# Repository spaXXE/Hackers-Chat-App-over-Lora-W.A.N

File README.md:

# Under rigorous Development...

***
### Watch out for exclusive tech. coming your way😎!

***

```py
    import time 

    def development():
        
        while 1:
            time.delay()
            break # DISCLAIMER: Heads up, will break soon...

    development()
```
***

***

   ### As an appetiser, we humbly offer you.....

***

## The Project's Structure.

## The Sofware's Components and Structure Model.

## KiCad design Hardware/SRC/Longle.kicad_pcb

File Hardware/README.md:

# LoRa Dongle

The hardware is a USB 2.0 fullspeed device with an STM32F042K6 MCU and 433MHz LoRa module based on the SX1278. Onboard EEPROM memory provides persistent storage of received messages and buffering of sent messages that have not been acknowledged to have been received by the sender.

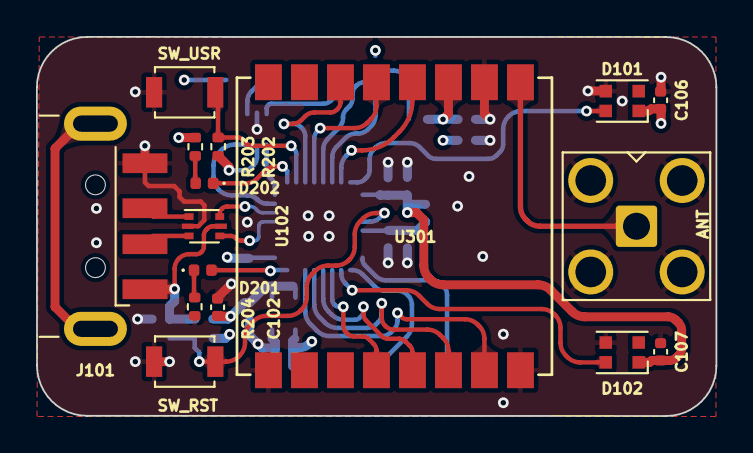
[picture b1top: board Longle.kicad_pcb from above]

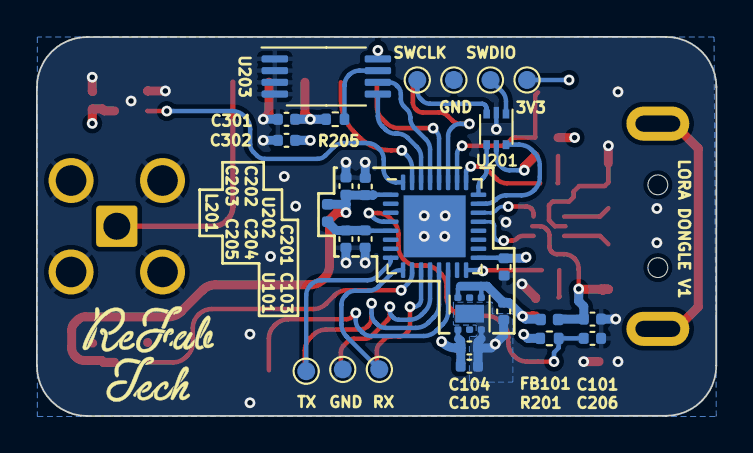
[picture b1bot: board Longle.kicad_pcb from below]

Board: 4 copper layers, 37.7 x 21.1 mm, 43 parts (27 on the bottom side), 34 nets.

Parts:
AE301: Antenna_Shield; SMA_Amphenol_901-143_Horizontal
C101, C102, C103, C104, C203, C204, C206, C301: 2u2; C_0402_1005Metric
C105, C106, C107, C201, C202, C205, C302: 100n; C_0402_1005Metric
D101, D102: WS2812B; LED_WS2812B-2020_PLCC4_2.0x2.0mm
D201: LED_O; LED_0402_1005Metric
D202: LED_B; LED_0402_1005Metric
FB101: 220R@100MHz 1A; L_0402_1005Metric
J101: USB_A; USB_A_CNCTech_1001-011-01101_Horizontal
L201: 10u; L_0402_1005Metric
R201, R202, R205: 10K 0.1%; R_0402_1005Metric
R203, R204: 1K 0.1%; R_0402_1005Metric
SW201: SW_RST; SW_SPST_B3U-1000P
SW202: SW_USER; SW_SPST_B3U-1000P
TP201: TP_3V3; TestPoint_Pad_D1.0mm
TP202: TP_SWDIO; TestPoint_Pad_D1.0mm
TP203: TP_GND1; TestPoint_Pad_D1.0mm
TP204: TP_SWCLK; TestPoint_Pad_D1.0mm
TP205: TP_TX; TestPoint_Pad_D1.0mm
TP206: TP_RX; TestPoint_Pad_D1.0mm
TP207: TP_GND2; TestPoint_Pad_D1.0mm
U101: TLV75533PDRV; WSON-6-1EP_2x2mm_P0.65mm_EP1x1.6mm
U102, U201: USBLC6-2P6; SOT-666
U202: STM32F042K6Ux; QFN-32-1EP_5x5mm_P0.5mm_EP3.45x3.45mm
U203: 24LC1025; TSSOP-8_4.4x3mm_P0.65mm
U301: Ai-Thinker-Ra-01; Ai-Thinker-Ra-01-LoRa

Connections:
+3V3: C104.1, C105.1, C106.1, C107.1, C201.1, C202.1, C203.1, C301.1, C302.1, D101.1 (VDD), D102.1 (VDD), L201.1, R201.1, R202.2, R203.2, R205.1, TP201.1, U101.1 (OUT), U201.5 (VBUS), U202.1 (VDD), U202.17 (VDDIO2), U203.8 (VCC), U301.3 (VDD)
+5V: C102.1, C103.1, FB101.2, U101.4 (EN), U101.6 (IN)
/D+: J101.3 (D+), U102.1 (I/O1)
/D-: J101.2 (D-), U102.3 (I/O2)
/RF_LORA_RA-01/ANT: AE301.1 (A), U301.1 (ANT)
/RF_LORA_RA-01/LORA_DIO0: U202.28 (PB5), U301.5 (DIO0)
/RF_LORA_RA-01/LORA_DIO1: U202.27 (PB4), U301.6 (DIO1)
/RF_LORA_RA-01/LORA_MISO: U202.12 (PA6), U301.13 (MISO)
/RF_LORA_RA-01/LORA_MOSI: U202.13 (PA7), U301.14 (MOSI)
/RF_LORA_RA-01/LORA_NCS: U202.14 (PB0), U301.15 (~NSS)
/RF_LORA_RA-01/LORA_RST: U202.31 (PF11), U301.4 (~RESET)
/RF_LORA_RA-01/LORA_SCK: U202.11 (PA5), U301.12 (SCK)
/STM32F042K6/BTN: R202.1, SW202.1, U202.26 (PB3)
/STM32F042K6/I2C1_SCL: U202.29 (PB6), U203.6 (SCL)
/STM32F042K6/I2C1_SDA: U202.30 (PB7), U203.5 (SDA)
/STM32F042K6/LED: D201.2 (A), U202.16 (PB2)
/STM32F042K6/NRST: C206.1, R201.2, SW201.2, U202.4 (NRST)
/STM32F042K6/SWCLK: U201.4 (I/O2), U202.24 (PA14)
/STM32F042K6/SWCLK_IN: TP204.1, U201.3 (I/O2)
/STM32F042K6/SWDIO: U201.6 (I/O1), U202.23 (PA13)
/STM32F042K6/SWDIO_IN: TP202.1, U201.1 (I/O1)
/STM32F042K6/USART2_RX: TP206.1, U202.9 (PA3)
/STM32F042K6/USART2_TX: TP205.1, U202.8 (PA2)
/STM32F042K6/USB_NOE: D202.1 (K), U202.25 (PA15)
/STM32F042K6/WS2812_1: D102.4 (DIN), U202.10 (PA4)
/STM32F042K6/WS2812_2: D101.4 (DIN), U202.32 (PB8)
/USB_DN: U102.4 (I/O2), U202.21 (PA11)
/USB_DP: U102.6 (I/O1), U202.22 (PA12)
GND: AE301.2 (Shield), C101.2, C102.2, C103.2, C104.2, C105.2, C106.2, C107.2, C201.2, C202.2, C203.2, C204.2, C205.2, C206.2, C301.2, C302.2, D101.3 (VSS), D102.3 (VSS), J101.4 (GND), R204.1, SW201.1, SW202.2, TP203.1, TP207.1, U101.3 (GND), U101.7 (GND), U102.2 (GND), U201.2 (GND), U202.33 (VSS), U203.1 (A0), U203.2 (A1), U203.3 (A2), U203.4 (GND), U301.2 (GND), U301.9 (GND), U301.16 (GND)
unnamed: D201.1 (K), R204.2
unnamed: D202.2 (A), R203.1
unnamed: R205.2, U203.7 (WP)
VBUS: C101.1, FB101.1, J101.1 (VBUS), U102.5 (VBUS)
VDDA: C204.1, C205.1, L201.2, U202.5 (VDDA)

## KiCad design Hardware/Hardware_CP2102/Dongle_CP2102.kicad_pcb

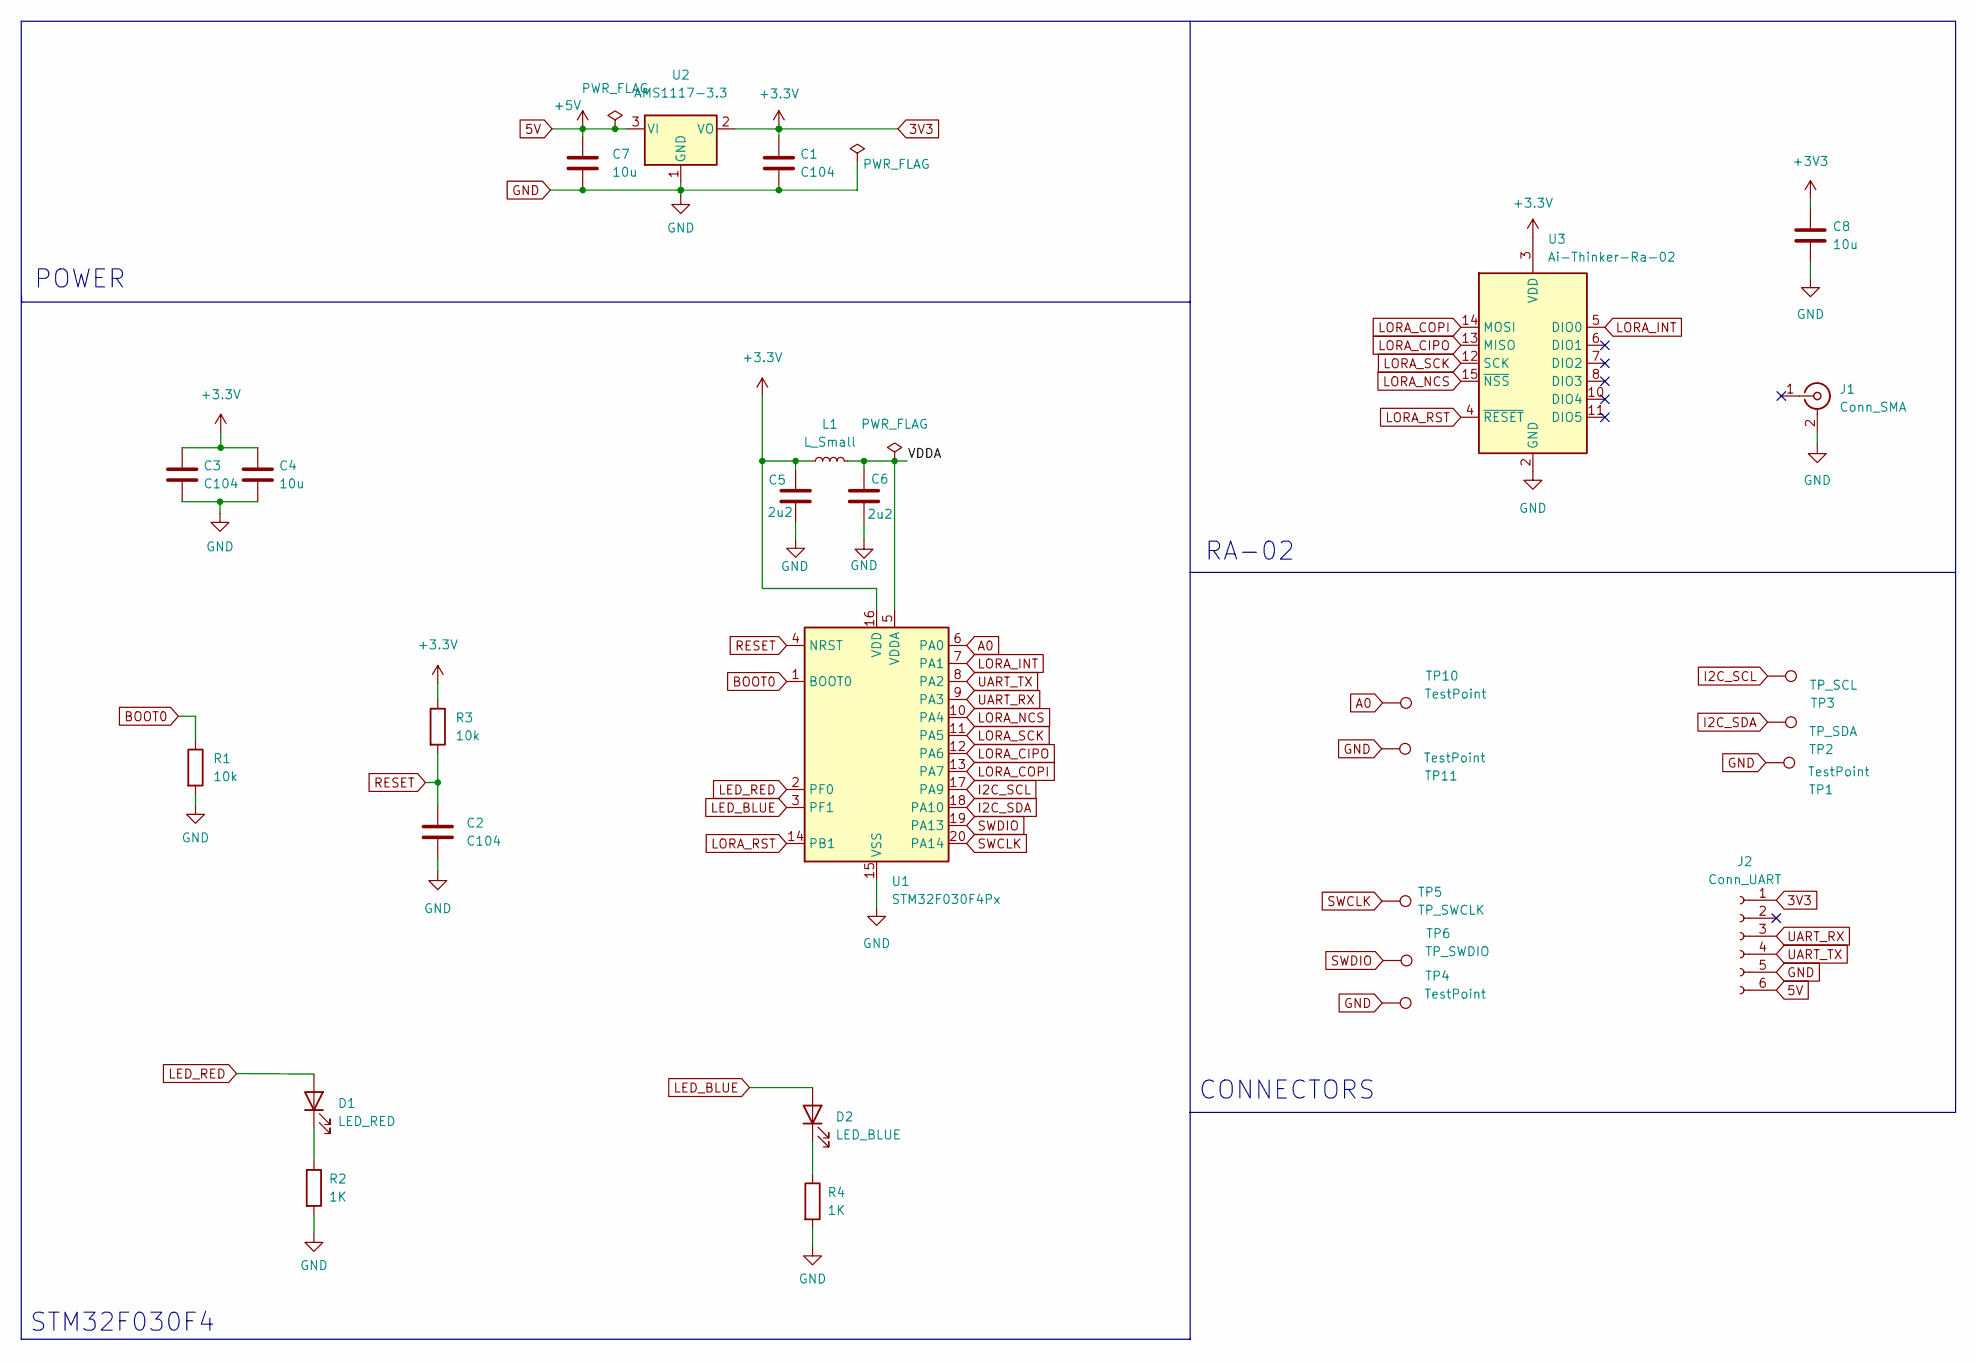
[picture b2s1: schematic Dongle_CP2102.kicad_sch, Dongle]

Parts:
C1, C2, C3: C104; C_0805_2012Metric_Pad1.18x1.45mm_HandSolder
C4, C7, C8: 10u; C_0805_2012Metric_Pad1.18x1.45mm_HandSolder
C5, C6: 2u2; C_0805_2012Metric_Pad1.18x1.45mm_HandSolder
D1: LED_RED; LED_0805_2012Metric_Pad1.15x1.40mm_HandSolder
D2: LED_BLUE; LED_0805_2012Metric_Pad1.15x1.40mm_HandSolder
J1: Conn_SMA; SMA_Amphenol_901-144_Vertical
J2: Conn_UART; PinSocket_1x06_P2.54mm_Horizontal
L1: L_Small; L_0805_2012Metric_Pad1.15x1.40mm_HandSolder
R1, R3: 10k; R_0805_2012Metric_Pad1.20x1.40mm_HandSolder
R2, R4: 1K; R_0805_2012Metric_Pad1.20x1.40mm_HandSolder
TP1, TP4, TP10, TP11: TestPoint; TestPoint_Pad_D1.5mm
TP2: TP_SDA; TestPoint_Pad_D1.5mm
TP3: TP_SCL; TestPoint_Pad_D1.5mm
TP5: TP_SWCLK; TestPoint_Pad_D1.5mm
TP6: TP_SWDIO; TestPoint_Pad_D1.5mm
U1: STM32F030F4Px; TSSOP-20_4.4x6.5mm_P0.65mm
U2: AMS1117-3.3; SOT-223-3_TabPin2
U3: Ai-Thinker-Ra-02; Ai-Thinker-Ra-01-LoRa

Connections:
3V3: C1.1, C3.1, C4.1, C5.1, C8.1, J2.1, L1.1, R3.1, U1.16 (VDD), U2.2 (VO), U3.3 (VDD)
5V: C7.1, J2.6, U2.3 (VI)
/VDDA: C6.1, L1.2, U1.5 (VDDA)
A0: TP10.1, U1.6 (PA0)
BOOT0: R1.1, U1.1 (BOOT0)
GND: C1.2, C2.2, C3.2, C4.2, C5.2, C6.2, C7.2, C8.2, J1.2 (Ext), J2.5, R1.2, R2.2, R4.2, TP1.1, TP4.1, TP11.1, U1.15 (VSS), U2.1 (GND), U3.1 (GND), U3.2 (GND), U3.9 (GND), U3.16 (GND)
I2C_SCL: TP3.1, U1.17 (PA9)
I2C_SDA: TP2.1, U1.18 (PA10)
LED_BLUE: D2.2 (A), U1.3 (PF1)
LED_RED: D1.2 (A), U1.2 (PF0)
LORA_CIPO: U1.12 (PA6), U3.13 (MISO)
LORA_COPI: U1.13 (PA7), U3.14 (MOSI)
LORA_INT: U1.7 (PA1), U3.5 (DIO0)
LORA_NCS: U1.10 (PA4), U3.15 (~NSS)
LORA_RST: U1.14 (PB1), U3.4 (~RESET)
LORA_SCK: U1.11 (PA5), U3.12 (SCK)
unnamed: D1.1 (K), R2.1
unnamed: D2.1 (K), R4.1
RESET: C2.1, R3.2, U1.4 (NRST)
SWCLK: TP5.1, U1.20 (PA14)
SWDIO: TP6.1, U1.19 (PA13)
UART_RX: J2.3, U1.9 (PA3)
UART_TX: J2.4, U1.8 (PA2)

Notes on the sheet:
STM32F030F4
CONNECTORS
RA-02
POWER

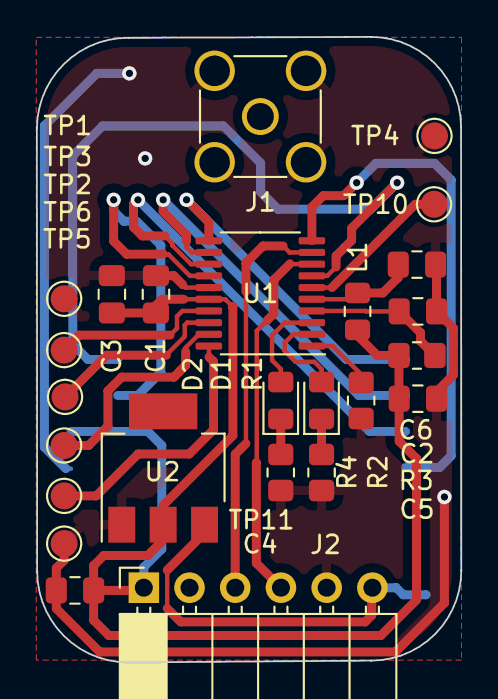
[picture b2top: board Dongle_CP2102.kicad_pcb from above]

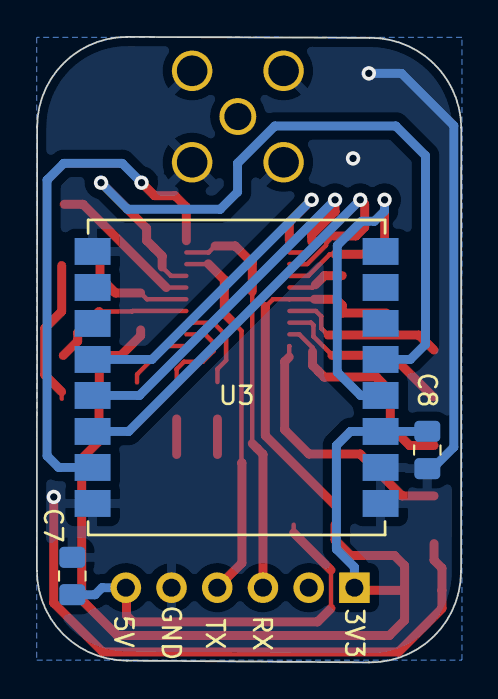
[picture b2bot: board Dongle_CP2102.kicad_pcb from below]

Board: 2 copper layers, 23.6 x 34.8 mm, 28 parts (3 on the bottom side), 23 nets.

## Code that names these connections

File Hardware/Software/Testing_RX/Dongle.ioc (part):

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Mcu.Name=STM32F030F4Px
Mcu.Package=TSSOP20
Mcu.UserName=STM32F030F4Px
PA0.Mode=IN0
PA0.Signal=ADC_IN0
PA1.GPIOParameters=GPIO_Label
PA1.GPIO_Label=LORA_INT
PA1.Signal=GPXTI1
PA10.Mode=I2C
PA10.Signal=I2C1_SDA
PA13.Mode=Serial_Wire
PA13.Signal=SYS_SWDIO
PA14.Mode=Serial_Wire
PA14.Signal=SYS_SWCLK
PA2.Mode=Asynchronous
PA2.Signal=USART1_TX
PA3.Mode=Asynchronous
PA3.Signal=USART1_RX
PA4.GPIOParameters=GPIO_Label
PA4.GPIO_Label=LORA_NCS
PA4.Signal=GPIO_Output
PA5.GPIOParameters=GPIO_Label
PA5.GPIO_Label=LORA_SCK
PA5.Mode=Full_Duplex_Master
PA5.Signal=SPI1_SCK
PA6.GPIOParameters=GPIO_Label
PA6.GPIO_Label=LORA_CIPO
PA6.Mode=Full_Duplex_Master
PA6.Signal=SPI1_MISO
PA7.GPIOParameters=GPIO_Label
PA7.GPIO_Label=LORA_COPI
PA7.Mode=Full_Duplex_Master
PA7.Signal=SPI1_MOSI
PA9.Mode=I2C
PA9.Signal=I2C1_SCL
PB1.GPIOParameters=GPIO_Label
PB1.GPIO_Label=LORA_RST
PB1.Signal=GPIO_Output
PF0-OSC_IN.GPIOParameters=GPIO_Label
PF0-OSC_IN.GPIO_Label=LED_RED
PF0-OSC_IN.Signal=GPIO_Output
PF1-OSC_OUT.GPIOParameters=GPIO_Label
PF1-OSC_OUT.GPIO_Label=LED_BLUE
PF1-OSC_OUT.Signal=GPIO_Output
RCC.HSE_VALUE=12000000
RCC.SYSCLKFreq_VALUE=48000000
RCC.SYSCLKSource=RCC_SYSCLKSOURCE_PLLCLK
board=custom

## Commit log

2022-11-04 Created a Readme file
2022-11-04 Created a .gitignore file.
2022-11-04 Added a README file.
2022-11-04 Added a .gitignore file
2022-11-04 Added a Mindmap of the Project Structure
2022-11-04 Added a Mindmap of the Project Structure.
2022-11-04 Added a Model of the Software Components and Structure.
2022-11-04 Added a Model of the Software's Components and Structure.
2022-11-04 Added a Mindmap of the Project's Structure.
2022-11-04 Messaged the world.
2022-11-04 Updated the Readme file.
2022-11-04 Added a dummy file
2022-11-10 Removed a folder.
2022-11-10 Created a folder for Hardware Dev.
2022-11-10 Added a folder for Hardware dev.
2022-11-10 Deleted a dummy file
2022-11-10 Deleted a dummy file.
2022-11-10 Create Test
2022-12-27 Added Hardware files
2023-06-22 Added dongle hardware files
2023-06-22 Added STM32 Pinout
2023-06-22 Created Hardware README
